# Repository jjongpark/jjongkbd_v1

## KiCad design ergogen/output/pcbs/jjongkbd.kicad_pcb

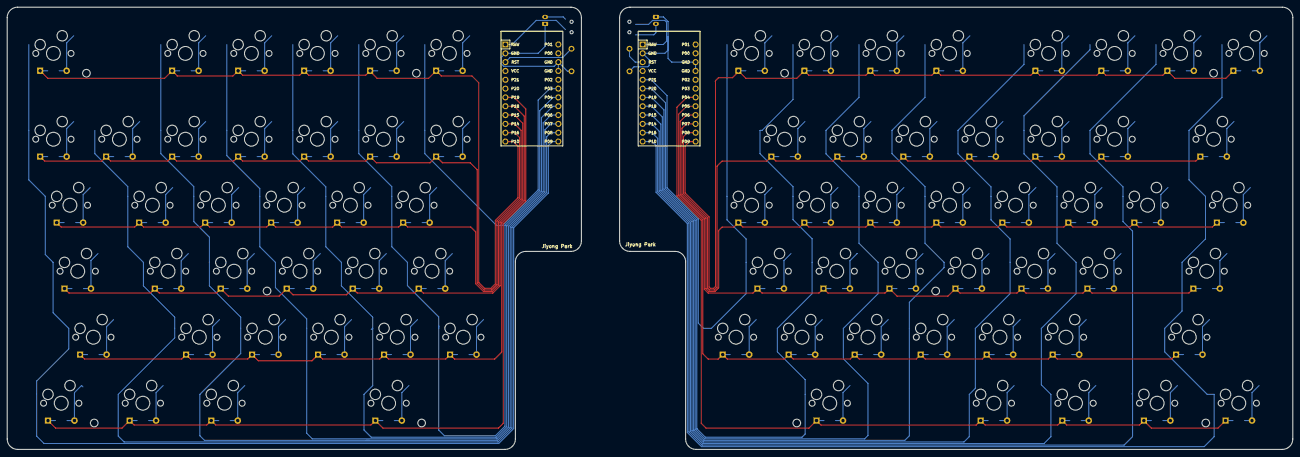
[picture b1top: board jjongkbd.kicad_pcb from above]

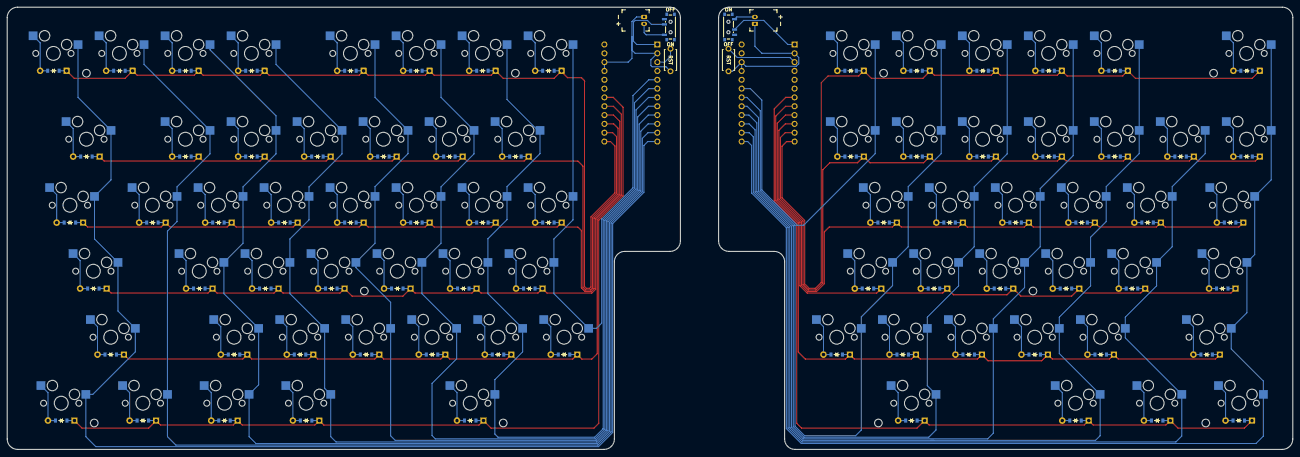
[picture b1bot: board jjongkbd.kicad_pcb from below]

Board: 2 copper layers, 370.1 x 127.3 mm, 172 parts (83 on the bottom side), 112 nets.

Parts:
D1, D2, D3, D4, D5, D6, D7, D8, D9, D10, D11, D12, D13, D14, D15, D16, D17, D18, D19, D20, D21, D22, D23, D24, D25, D26, D27, D28, D29, D30, D31, D32, D33, D34, D35, D36, D37, D38, D39, D40, D41, D42, D43, D44, D45, D46, D47, D48, D49, D50, D51, D52, D53, D54, D55, D56, D57, D58, D59, D60, D61, D62, D63, D64, D65, D66, D67, D68, D69, D70, D71, D72, D73, D74, D75, D76, D77: diode_tht_sod123
JST1, JST2: battery_connector_jst_ph_2
MCU1, MCU2: ProMicro
MH1, MH2, MH3, MH4, MH5, MH6, MH7, MH8, MH9, MH10: mounting_hole_npth
PWR1, PWR2: power_switch_smd_side
RST1, RST2: reset_switch_tht_top
S1, S2, S3, S4, S5, S6, S7, S8, S9, S10, S11, S12, S13, S14, S15, S16, S17, S18, S19, S20, S21, S22, S23, S24, S25, S26, S27, S28, S29, S30, S31, S32, S33, S34, S35, S36, S37, S38, S39, S40, S41, S42, S43, S44, S45, S46, S47, S48, S49, S50, S51, S52, S53, S54, S55, S56, S57, S58, S59, S60, S61, S62, S63, S64, S65, S66, S67, S68, S69, S70, S71, S72, S73, S74, S75, S76, S77: MX

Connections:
LBAT: JST1.2, PWR1.1
LC1: MCU1.24, S1.1, S7.1, S14.1, S20.1, S26.1, S32.1
LC2: MCU1.23, S8.1, S15.1, S21.1, S27.1, S33.1
LC3: MCU1.22, S2.1, S9.1, S16.1, S22.1, S28.1, S34.1
LC4: MCU1.21, S3.1, S10.1, S17.1, S23.1, S29.1
LC5: MCU1.20, S4.1, S11.1, S18.1, S24.1, S30.1, S35.1
LC6: MCU1.19, S5.1, S12.1, S19.1, S25.1, S31.1
LC7: MCU1.18, S6.1, S13.1
LGND: JST1.1, MCU1.2, MCU1.15, MCU1.16, RST1.2
LR1: D1.1, D2.1, D3.1, D4.1, D5.1, D6.1, MCU1.12
LR2: D7.1, D8.1, D9.1, D10.1, D11.1, D12.1, D13.1, MCU1.11
LR3: D14.1, D15.1, D16.1, D17.1, D18.1, D19.1, MCU1.10
LR4: D20.1, D21.1, D22.1, D23.1, D24.1, D25.1, MCU1.9
LR5: D26.1, D27.1, D28.1, D29.1, D30.1, D31.1, MCU1.8
LR6: D32.1, D33.1, D34.1, D35.1, MCU1.7
LRAW: MCU1.1, PWR1.2
LRST: MCU1.3, RST1.1
RBAT: JST2.2, PWR2.1
RC1: MCU2.5, S47.1, S54.1, S62.1, S77.1
RC2: MCU2.6, S40.1, S46.1, S53.1, S61.1, S69.1, S76.1
RC3: MCU2.7, S45.1, S52.1, S60.1, S68.1, S75.1
RC4: MCU2.8, S44.1, S51.1, S59.1, S67.1, S74.1
RC5: MCU2.9, S39.1, S43.1, S50.1, S58.1, S66.1, S73.1
RC6: MCU2.10, S38.1, S42.1, S49.1, S57.1, S65.1, S72.1
RC7: MCU2.11, S37.1, S56.1, S64.1, S71.1
RC8: MCU2.12, S36.1, S41.1, S48.1, S55.1, S63.1, S70.1
RGND: JST2.1, MCU2.2, MCU2.15, MCU2.16, RST2.2
RR1: D70.1, D71.1, D72.1, D73.1, D74.1, D75.1, D76.1, D77.1, MCU2.24
RR2: D63.1, D64.1, D65.1, D66.1, D67.1, D68.1, D69.1, MCU2.23
RR3: D55.1, D56.1, D57.1, D58.1, D59.1, D60.1, D61.1, D62.1, MCU2.22
RR4: D48.1, D49.1, D50.1, D51.1, D52.1, D53.1, D54.1, MCU2.21
RR5: D41.1, D42.1, D43.1, D44.1, D45.1, D46.1, D47.1, MCU2.20
RR6: D36.1, D37.1, D38.1, D39.1, D40.1, MCU2.19
RRAW: MCU2.1, PWR2.2
RRST: MCU2.3, RST2.1
bottom_b: D31.2, S31.2
bottom_b_r: D47.2, S47.2
bottom_c: D29.2, S29.2
bottom_comma: D44.2, S44.2
bottom_m: D45.2, S45.2
bottom_n: D46.2, S46.2
bottom_period: D43.2, S43.2
bottom_shift: D26.2, S26.2
bottom_shift_r: D41.2, S41.2
bottom_slash: D42.2, S42.2
bottom_v: D30.2, S30.2
bottom_x: D28.2, S28.2
bottom_z: D27.2, S27.2
function_esc: D1.2, S1.2
function_f1: D2.2, S2.2
function_f2: D3.2, S3.2
function_f3: D4.2, S4.2
function_f4: D5.2, S5.2
function_f5: D6.2, S6.2
function_f5_r: D77.2, S77.2
function_f6: D76.2, S76.2
function_f7: D75.2, S75.2
function_f8: D74.2, S74.2
function_f9: D73.2, S73.2
function_f10: D72.2, S72.2
function_f11: D71.2, S71.2
function_f12: D70.2, S70.2
meta_alt: D34.2, S34.2
meta_alt_r: D39.2, S39.2
meta_ctrl: D32.2, S32.2
meta_ctrl_r: D36.2, S36.2
meta_fn: D38.2, S38.2
meta_meta: D37.2, S37.2
meta_space: D35.2, S35.2
meta_space_r: D40.2, S40.2
meta_win: D33.2, S33.2
mid_a: D21.2, S21.2
mid_caps: D20.2, S20.2
mid_colon: D50.2, S50.2
mid_d: D23.2, S23.2
mid_enter: D48.2, S48.2
mid_f: D24.2, S24.2
mid_g: D25.2, S25.2
mid_h: D54.2, S54.2
mid_j: D53.2, S53.2
mid_k: D52.2, S52.2
mid_l: D51.2, S51.2
mid_quote: D49.2, S49.2
mid_s: D22.2, S22.2
num_backspace: D63.2, S63.2
num_eight: D68.2, S68.2
num_five: D12.2, S12.2
num_four: D11.2, S11.2
num_minus: D65.2, S65.2
num_nine: D67.2, S67.2
num_one: D8.2, S8.2
num_plus: D64.2, S64.2
num_seven: D69.2, S69.2
num_six: D13.2, S13.2
num_three: D10.2, S10.2
num_tilda: D7.2, S7.2
num_two: D9.2, S9.2
num_zero: D66.2, S66.2
top_e: D17.2, S17.2
top_i: D60.2, S60.2
top_left_paren: D57.2, S57.2
top_o: D59.2, S59.2
top_p: D58.2, S58.2
top_pipe: D55.2, S55.2
top_q: D15.2, S15.2
top_r: D18.2, S18.2
top_right_paren: D56.2, S56.2
top_t: D19.2, S19.2
top_tab: D14.2, S14.2
top_u: D61.2, S61.2
top_w: D16.2, S16.2
top_y: D62.2, S62.2

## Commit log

2025-05-21 initial
2025-06-12 Final result
2025-06-12 Ignore .DS_Store
2025-06-12 Actually remove .DS_Store files
2025-06-12 Add zmk files
